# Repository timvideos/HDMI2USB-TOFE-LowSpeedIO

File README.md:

The <a href="http://hdmi2usb.tv/numato-opsis">Numato Opsis</a>, the first open hardware for the
<a href="http://hdmi2usb.tv">HDMI2USB firmware</a>,
<a href="https://numato.com/product/numato-opsis-fpga-based-open-video-platform">can now be ordered from Numato Labs
</a>

## Low Speed I/O - TOFE Expansion board

While the [Numato Opsis board](https://numato.com/product/numato-opsis-fpga-based-open-video-platform)
has a massive amount of high speed I/O interfaces, it doesn't include many
features for interfacing with more pedestrian speed devices such as buttons or
LEDs. To help solve this problem “Low speed I/O” TOFE expansion board was
created.

## Features

The "Low Speed I/O" board has the following features;

 * 1 x Arduino compatible pin header. (With on board ADC enabling analog pins
   support.)

 * 4 x [Digilent Pmod™ Compatible](http://www.digilentinc.com/Pmods/licensing.cfm)
   headers[1] to allow usage of existing expansion boards,
   including boards from 
   [Numato Lab](http://numato.com/fpga-boards/filter/cat/expansion-modules.html?limit=30),
   [Digilent](http://digilentinc.com/pmods),
   [Maxim](https://www.maximintegrated.com/en/design/design-technology/fpga-design-resources/pmod-compatible-plug-in-peripheral-modules.html) and
   [Analog](https://wiki.analog.com/resources/alliances/xilinx#pmods).

 * 1 x USB-UART, allowing low speed serial operation.

 * 6 x Indicator LEDs

 * 4 x Push Buttons

[1]: Two of the Pmod headers share pins with the Arduino header. This means
that when the Arduino compatible pin header is in use only 2 Pmod headers are
available.

A PDF version of schematic can be found in the [docs](docs) directory.

## Editing

The design in this repository was made using [KiCad](http://www.kicad-pcb.org/)
version **2013-07-07 BZR 4022**
([the version is Ubuntu Trusty](http://packages.ubuntu.com/trusty/kicad)).

## License

TOFE Low Speed I/O Expansion board by Numato Systems Pvt. Ltd

The TOFE Low Speed I/O Expansion board is licensed under a
Creative Commons Attribution-ShareAlike 4.0 International License.

You should have received a copy of the license along with this
work. If not, see <http://creativecommons.org/licenses/by-sa/4.0/>.

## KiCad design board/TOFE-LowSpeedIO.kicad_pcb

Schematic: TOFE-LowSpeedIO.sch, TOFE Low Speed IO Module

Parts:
C1, C2: 22pF
C3, C4, C10: 0.1uF
C8, C9: 100uF
D1, D2, D3, D5, D6, D7: LED
D4: DIODE
P1, P2, P3, P4: CONN_6X2
P5: CONN_2
P6: CONN_6
R1, R2, R3, R5, R6, R7, R8, R9: 10K
R4: 680R
R10: 100R
SW1, SW2, SW3, SW4: SW_PUSH
U1: TOFE-8X
U2: AURD_COMM_SHIELD_ZERO_NEW
U3: PIC18F14K50
U5: 7805_NW
X1: CRYSTAL
X2: USBMICRO

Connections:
/12V: D4.1 (A), U1.A2 (12V), U1.A3 (12V), U1.B1 (12V), U1.B2 (12V), U1.B3 (12V)
/A0: U2.9 (A0), U3.9 (RC7/AN9/SDO/T1OSC0)
/A1: U2.10 (A1), U3.8 (RC6/AN8/T13CKI/T1OSC1)
/A2: U2.11 (A2), U3.7 (RC3/AN7/P1C/C12IN3/PGM)
/A3: U2.12 (A3), U3.16 (RC0/AN4/C12IN+/INT0/VREF+)
/A4: U2.13 (A4), U3.15 (RC1/AN5/C12IN1-/INT1/VREF-)
/A5: U2.14 (A5), U3.14 (RC2/AN6/P1D/C12IN2/CVREF/INT2)
/AREF: R3.2, U1.B37 (DIFF_IO_B5P), U2.30 (AREF)
/ATN: U1.A44 (DIFF_IO_A6N), U2.1 (ATN)
/D0: P4.7, U1.B12 (DIFF_IO_YN), U2.15 (0/RX)
/D1: P4.1, U1.B14 (DIFF_IO_B1P), U2.16 (1/TX)
/D2: P4.8, U1.B15 (DIFF_IO_B1N), U2.17 (2)
/D3: P4.2, U1.B19 (DIFF_IO_B2P), U2.18 (3/PWM)
/D4: P4.9, U1.B20 (DIFF_IO_B2N), U2.19 (4)
/D5: P4.3, U1.A19 (DIFF_IO_YP), U2.20 (5/PWM)
/D6: P4.10, U1.B24 (DIFF_IO_B3N), U2.21 (6/PWM)
/D7: P4.4, U1.B23 (DIFF_IO_B3P), U2.22 (7)
/D8: P3.7, U1.B28 (DIFF_CLK_B0N), U2.23 (8)
/D9: P3.1, U1.B27 (DIFF_CLK_B0P), U2.24 (9/PWM)
/D10: P3.8, U1.B30 (DIFF_IO_ZN), U2.25 (10/PWM/SS)
/D11: P3.2, U1.A32 (DIFF_IO_ZP), U2.26 (11/PWM/SPI_MOSI), U2.P4 (SPI_MOSI)
/D12: P3.9, U1.B33 (DIFF_IO_B4P), U2.27 (12/SPI_MIS0), U2.P1 (SPI_MISO)
/D13: P3.3, U1.B34 (DIFF_IO_B4N), U2.28 (13/PWM/SPI_SCK), U2.P3 (SPI_SCK)
/D14: P3.10, U1.B38 (DIFF_IO_B5N), U2.31 (SDA)
/D15: P3.4, U1.B41 (DIFF_IO_B6P), U2.32 (SCL)
/GND: C1.1, C2.1, C3.1, C4.1, C8.2, C9.2, C10.2, D1.2, D2.2, D3.2, D5.2, D6.2, D7.2, P1.5, P1.11, P2.5, P2.11, P3.5, P3.11, P4.5, P4.11, P5.2 (PM), P6.3, R10.2, SW1.2, SW2.2, SW3.2, SW4.2, U1.A4 (GND), U1.A12 (GND), U1.A15 (GND), U1.A18 (GND), U1.A20 (GND), U1.A23 (GND), U1.A24 (GND), U1.A27 (GND), U1.A28 (GND), U1.A31 (GND), U1.A34 (GND), U1.A37 (GND), U1.A38 (GND), U1.A41 (GND), U1.A42 (GND), U1.A45 (GND), U1.A46 (GND), U1.A49 (GND), U1.B4 (GND), U1.B7 (GND), U1.B13 (GND), U1.B16 (GND), U1.B18 (GND), U1.B21 (GND), U1.B22 (GND), U1.B25 (GND), U1.B26 (GND), U1.B29 (GND), U1.B32 (GND), U1.B35 (GND), U1.B36 (GND), U1.B39 (GND), U1.B40 (GND), U1.B43 (GND), U1.B44 (GND), U1.B47 (GND), U1.B49 (GND), U2.6 (GND), U2.7 (GND), U2.29 (GND), U2.P6 (GND), U3.20 (VSS), U5.2 (GND), X2.5 (GND); also elsewhere on the board
/GPIO0_N: P1.7, U1.A6 (DIFF_IO_A0N)
/GPIO0_P: P1.1, U1.A5 (DIFF_IO_A0P)
/GPIO1_N: P1.8, U1.A8 (DIFF_IO_B0N)
/GPIO1_P: P1.2, U1.A7 (DIFF_IO_B0P)
/GPIO2_N: P1.9, U1.A14 (DIFF_CLK_XN)
/GPIO2_P: P1.3, U1.A13 (DIFF_CLK_XP)
/GPIO3_N: P1.10, U1.A17 (DIFF_IO_A1N)
/GPIO3_P: P1.4, U1.A16 (DIFF_IO_A1P)
/GPIO4_N: P2.7, U1.A22 (DIFF_IO_A2N)
/GPIO4_P: P2.1, U1.A21 (DIFF_IO_A2P)
/GPIO5_N: P2.8, U1.A26 (DIFF_IO_A3N)
/GPIO5_P: P2.2, U1.A25 (DIFF_IO_A3P)
/GPIO6_N: P2.9, U1.A30 (DIFF_CLK_A0N)
/GPIO6_P: P2.3, U1.A29 (DIFF_CLK_A0P)
/GPIO7_N: P2.10, U1.A36 (DIFF_IO_A4N)
/GPIO7_P: P2.4, U1.A35 (DIFF_IO_A4P)
/LED1: R5.7, U1.A39 (DIFF_IO_A5P)
/LED2: R5.5, U1.A40 (DIFF_IO_A5N)
/LED3: R5.3, U1.B42 (DIFF_IO_B6N)
/LED4: R5.1, U1.A43 (DIFF_IO_A6P)
/PGC: P6.5, U3.18 (D-/PGC), X2.2 (D-)
/PGD: P6.4, U3.19 (D+/PGD), X2.3 (D+)
/RESET: U1.A11 (~RST), U2.3 (RESET), U2.P5 (RESET)
/RX: U1.B11 (DIFF_IO_XN), U3.12 (RB5/AN11/RX/DT)
/SCL: R8.1, U1.B5 (IDCLK), U3.11 (RB6/SCK/SCL)
/SDA: R9.1, U1.B6 (IDDAT), U3.13 (RB4/AN10/SDI/SDA)
/SW1: R4.7, U1.B45 (DIFF_CLK_B1P)
/SW2: R4.5, U1.B46 (DIFF_CLK_B1N)
/SW3: R4.3, U1.A47 (DIFF_CLK_A1P)
/SW4: R4.1, U1.A48 (DIFF_CLK_A1N)
/TX: U1.B9 (DIFF_IO_XP), U3.10 (RB7/TX/CK)
/VCC3V3: C4.2, P1.6, P1.12, P2.6, P2.12, P3.6, P3.12, P4.6, P4.12, P6.2, R1.1, R3.1, R6.2, R8.2, R9.2, U1.A9 (3V3), U1.A10 (3V3), U1.B8 (3V3), U1.B10 (3V3), U2.4 (3V3), U3.1 (VDD)
/VCC5V: C9.1, C10.1, U2.5 (5V), U2.P2 (5V), U5.3 (VO)
/VCC12V: C8.1, D4.2 (K), U2.8 (VIN), U5.1 (VI)
/VPP: P5.1, P6.1, R1.2, U3.4 (RA3/MCLR/VPP)
unnamed: C1.2, U3.3 (RA4/AN3/OSC2/CLKO), X1.2
unnamed: C2.2, U3.2 (RA5/OSC1/CLKI), X1.1
unnamed: C3.2, U3.17 (VUSB)
unnamed: D1.1, R5.8
unnamed: D2.1, R5.6
unnamed: D3.1, R5.4
unnamed: D5.1, R2.2
unnamed: D6.1, R7.2
unnamed: D7.1, R5.2
unnamed: R2.1, U3.5 (RC5/CCP1/P1A/T0CKI)
unnamed: R4.2, SW4.1
unnamed: R4.4, SW3.1
unnamed: R4.6, SW2.1
unnamed: R4.8, SW1.1
unnamed: R6.1, U2.2 (IOREF)
unnamed: R7.1, U3.6 (RC4/P1B/C12OUT/SRQ)
unnamed: R10.1, X2.1 (VUSB)

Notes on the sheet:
EXPANSION CONNECTORS
PUSH BUTTON SWITCH
LED
ARDUINO ZERO SHIELD
TOFE
12Mhz
ICSP
FWUP
POWER SUPPLY
PIC18F14K50

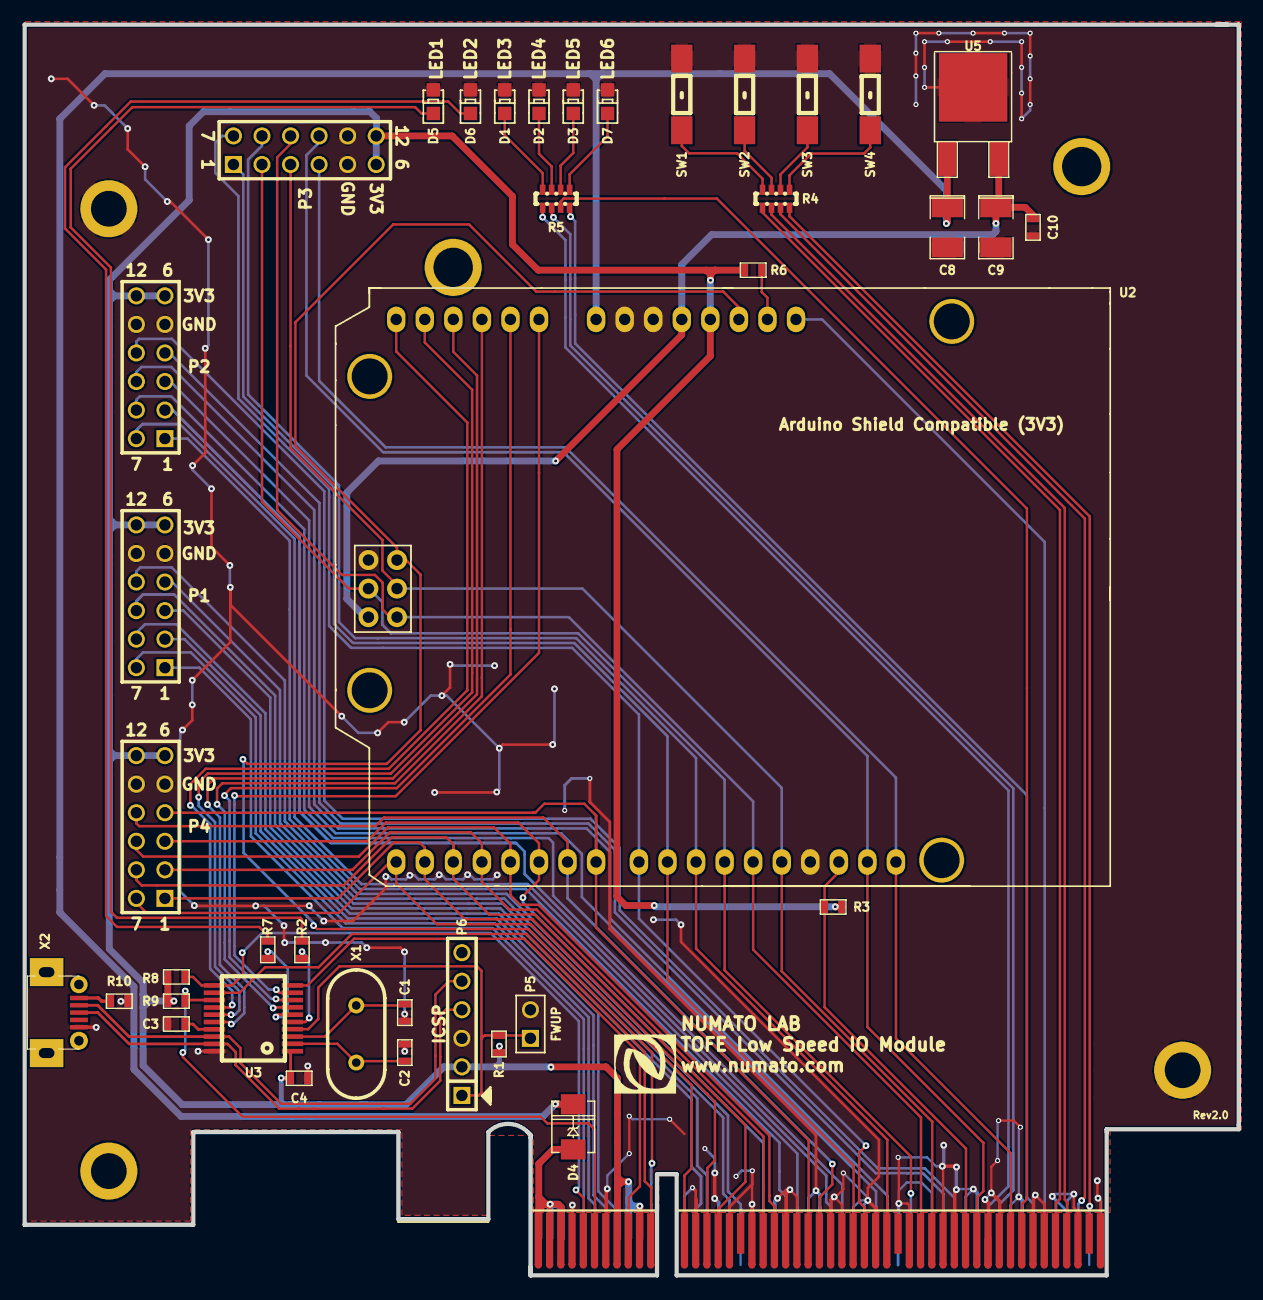
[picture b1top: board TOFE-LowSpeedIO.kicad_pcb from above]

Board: 2 copper layers, 108.0 x 111.2 mm, 42 parts (0 on the bottom side), 78 nets.

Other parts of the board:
1PIN: P***; MH-3.2MM
1PIN#2: P***; 1pin

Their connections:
/GND: 1PIN#2.0; also elsewhere on the board

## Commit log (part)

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2011-12-18 Added eeReadByte() and eeWriteByte() for utilizing the EEPROM. BXR
    Usage:
    eeSetup()
    BP_EE_WP = 0;
    Perform read and writes now.
2011-12-19 Added define functions to enable or disable write protection: // couple defines to enable and disable WP #define eeEnableWrite() BP_EE_WP=0 #define eeDisableWrite() BP_EE_WP=1 #define eeGetWP() BP_EE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
2011-12-19 Enabled the 'h' command for command history. Per Ian I used a define to re-disable it in base.h BP_ENABLE_HISTORY. Seems to be working good so im not sure why it was disabled. but incase it was for a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
2011-12-19 Testing all the small changes for v4 on the v3. I found some small errors in the translation files. Now fixed (project missed the en_US.h include. now fixed works great on v3! BXR
2011-12-19 Updated RC5 decoder as recommended: http://dangerousprototypes.com/forum/viewtopic.php?f=29&t=3342&view=unread#p32861
2011-12-20 v3 reset emulation for testing AVRdude on v4
2011-12-21 AVRDude 40x speedup improvement. WARNING: uses polling of UART bits, will not work on v4 yet! Needs AVRDude patch to work: http://dangerousprototypes.com/forum/viewtopic.php?f=41&t=2629
2011-12-21 bpv4 binary mode reset small fix to include command prompt
2011-12-21 Fixed v4 PPS for LCD, SPI, and UART. AUX pin still needed.
2011-12-22 IR Toy usb stack updates from JTR, fixes 48 byte bug http://dangerousprototypes.com/forum/viewtopic.php?f=29&t=3142&start=15#p33124
2011-12-22 Bus Pirate v3.5e and v4c: centered USB and Connector for both boards LEDs and connectors positions are same on both boards
2011-12-23 Added the 'e' command text to BPMSG instead of bpWline's. BXR
2011-12-25 Changed the Detect Baud rate option to show details so users can see what baud rate was detected and deleted un-needed bpWline messages so no translations needed. BXR
2011-12-26 Deleted a development string I left in base.h. Also renamed the Baud Detection enable define to somthing more understandable. BXR
2011-12-27 part pirate or part ninja silicone tester.
2011-12-28 I checked UART to ensure PPS defines work and UART worked fine. I did not test other peripherals. I also added AUX1 and AUX2 to the PPS controls for hardwarev4a.h
2011-12-28 Cleanup a little bit. Added the on-board EEPROM defines (address,min,max,...). Added the only other broken out PINs PPS (why not) ADC. added 'BP_BUTTON_ISDOWN' define (so you can 'if(BP_BUTTON_ISDOWN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
2011-12-30 Added a 'getlong' function; exactly the same as 'getnumber' but allows a larger MAX value. Enabled on BUSPIRATEV4 ONLY
2011-12-30 Fixed an issue with the new BRG calculation macro and added the text to BPMSG translation files. BXR
2011-12-30 Deleted the BRG calculation macro now that you can input a custom BAUD instead of BRG value now anyways. Deleted translations as they are no longer used. BXR
2012-01-02 Bus Pirate PIC programmer v1c for BPv3
2012-01-04 Connected A10, A11, A12, MEMW and MEMR to CPLD. Texts and labels needs to be fixed
2012-01-04 more updates: moved holes' center 4mm from the corner, holes are not plated, moved push buttons of v4c moved ICSP connectors of v3.5e and v5c moved USB connectors of v3.5e and v5c
2012-01-04 hex2prog added for Bus Pirate bootloader upgrader app
2012-01-04 Bus Pirate documents folder from old SVN
2012-01-04 Edited build-unix.sh and added Linux version for pirate-loader and test script
2012-01-05 BusPirate 4c Sketchup model and one rendering of the same
2012-01-06 Rendering and Sketchup model of the Bus Pirate 3.5e SSOP
2012-01-07 -made adjustments to the labels on the board
2012-01-08 Baud detection updates per Ians v6.1 list. Including: Much smarter 'get nearest common baud' function. MUCH SMARTER Macro still exists for both v3 and v4 hardware Less text used for macro and setup s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
2012-01-09 Bus Pirate SUMP mode fix (made mode variable static again)
2012-01-09 bus pirate hardware version detect
2012-01-09 Bus Pirate bitbang mode IO fix: http://dangerousprototypes.com/forum/viewtopic.php?f=28&t=3403&p=34198#p34196
    Thanks tes!
2012-01-09 defaul unit set to mil, change default trace width to 12mil, drill size to 20. Rename remove_label_layers.scr to hide_label_layers.scr
2012-01-09 Awesome optimization of the get estimated baud function with Arhis help. Same finish but less code to get there. BXR
2012-01-10 Decided there may be more macros or somthing that need to check and offer to match settings. So I moved it into a function UARTmatchSetup(). The function is enabled/disabled by the same define and BP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
2012-01-10 Removal of match baud. BXR
2012-01-12 Just fixed a small warning about unused variable message upon building by putting it behind a hardware version define (BUSPIRATEV2)? in Main.c BXR
2012-01-13 Added SOD-123 package for DIODE device
2012-01-15 Initial programming adapter for BPv4 schematic added, SMPS code does not block other BP functions
2012-01-16 Added LM321 op amp in SOT-23-5 package
2012-01-16 Soldering iron Driver based on arhis Gen3 design
2012-01-17 -updated standard PCB footprints with the latest design
2012-01-18 SOPA PIPA banners
2012-01-18 initial version of the freestanding USB stack, based on the revision 1599 of echo-demo
2012-01-19 removed hole, just plain pad on the 4.1mm round pad package
2012-01-19 Updated standard PCB footprints and added new PCB footprints
2012-01-20 Pic programmer v2 component placement and routing changed for making it smaller
2012-01-23 include grid alternate grid unit, turn-on grid.
2012-01-27 Mass clean-up, rename to a more logical naming. Removed duplicates on symbols and package.
2012-01-30 3d model of the web platform 1.1a
2012-02-02 redesign PCB symbol, added keepout on the DP6037 pcb
2012-02-06 Part Ninja, v1, board, schematic and gerbers
2012-02-06 updated DP6037 standard PCB footprint
2012-02-08 Logo for CC-0 and CC-BY-SA added
2012-02-08 BP4 LCD adapter V4 on a standard case, along with gerbers
2012-02-08 fix 4.1mm round pad, turned on the solder mask "stop" on the pad's property
2012-02-09 updated librarydefaults
2012-02-09 fixed DP10062_V1. removed duplicated holes that gives an error in DRC
2012-02-09 Adding a few SketchUp 3D models.
2012-02-13 Added new board for XTIDE CPLD 3V3 v2a with labels for credits on peitja, J1mbo, alanh and for the Vintage Computer Forums
2012-02-13 Bus Pirate 3.5c sketchup 3d model
2012-02-13 Adding CH375 "USB host Interface Chip" symbol and part to the library the cell SOIC28W already exists. see http://dangerousprototypes.com/forum/viewtopic.php?f=19&t=2657&start=255#p34828
2012-02-14 revered to Jer's 1658 PCBs
2012-02-15 updated v3.5 and v4 board to the new DP6037 standard PCB
2012-02-16 updated BP accessories: HV programming adapter for bus pirate V3 and V4 Made the female IO header location fixed with the Bus Pirate IO header 8.5mm from board edge in x axis.
2012-02-16 updated v1.2 board, moved CC-BY-SA license and OSHW logo to bottom. Made gerber files
2012-02-17 Added BusBlaster-v3.5 board in a standard DP8049 PCB.
2012-02-17 updated XC2C64A v1c and XC9572XL v1b with license CC-0, OSHW and DP logos on the bottom.
2012-02-20 Updated USBPOVToy.v1c board, added logo on the bottom pcb.
2012-02-27 Micro constant Current from SQKYbeaver
2012-02-29 Moveing PIC32Dip files into the hardwar folder insted of root
2012-02-29 PIC32DIP, made some BOM shanges (adjusted the Cap values
2012-03-01 project rebuild, and hex file for the PIC32DIP self test
2012-03-05 Logic Shrimp 3D model
2012-03-07 Updated to the valuse of discrete components on the schematic for Part Ninja
2012-03-07 Updates tot he pic18f2550 schematic, and export files
2012-03-10 Updated the pic24 and pic32 coic28 BB schematic Values
2012-03-12 updated board, widen up spaces, add CC-0 and OSHW logos.
2012-03-12 change version to V1a, board is now consistent on version 1771 schematic.
2012-03-12 Change version to V1a Breakout pin 23 and add Soldering jumper going to 3.3V in case USB mode is used.
2012-03-13 Dangerous Prototypes conference materials
2012-03-13 Map of Cheonggyecheon SVG, and PNG
2012-03-14 Reverted v1's gerber and images. Added v1a gerber and images too.
2012-03-14 reverted v1 board and schematic image and gerber. Added v1a board and schematic image and gerber
2012-03-15 Modification to the Sketchup 3d Models. Adding 2 models, modifying the pinhead models.
2012-03-19 pic32dip partlist wik file
2012-03-26 3d model of picquen32 v1a
2012-03-27 Added Linux Makefile to BPXSVFPlayer folder and compiled binary to package folder
2012-03-28 Demo Mode LED blinking demo for the Bus pirate, zipped up project files
2012-03-28 updates to the BP demo blink led
2012-03-29 update DP eagle library, added ATMEGA32U4, MAX6921. updated the SOIC-28W package to have a larger pads, updated small tactile switch footprint to have a larger pads too. fix center of VFD IV 22 displ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
2012-04-05 Fixes that annoying 'unsued var i' error
2012-04-11 Fix Transistor 5, swapped its collector and emitter.
2012-04-11 PiratePicProg: Fix fatal error, when calling BP_Flush with empty buffer.
2012-04-12 PiratePICProg: Commited patches from AndThen (PIC32MX), PIC32 still needs work. Added verbose debugging print (so far buspirate and serial module). Fixed PIC24 readout support, fixed endiannes of rea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
2012-04-24 renamed bus blaster v3 and v2.7 to match conventions
2012-04-24 updates to SMPS files for binmode usability.
2012-04-25 Buspirate: new PIC programming protocol added to binwire.c
2012-04-26 ATX breakout commit
2012-04-26 yongsan map made in inkscape
2012-04-26 renamed atx v1 breakout eagle files
2012-04-26 Add Standard DP PCB eagle library
2012-04-26 Link to the google SU plugin for exporting faces to SVG.
2012-04-27 Added: USB micro-b, LTC4053, removed eagle lite unsopported DP PCB sizes from dp_pcb.lbr
2012-05-01 Bus Pirate on standard PCB format.
2012-05-01 lcd adapter history file
2012-05-01 Added 3D Parts from my collection
2012-05-01 Bus Pirate v3.6 manufacturing resources
2012-05-02 renameing and small value changes to Bus Blaster v3.5, now V3b. also added new gerbers, partlist, and quote package. v3,5 removed
2012-05-02 Bus Blaster v3 JTAGkey buffer with self test
2012-05-02 Added integrated support of XSVF player for BPv4 only Added Windows side XSVF Player for BPv4 only (Built with Dev-C++) Has been based on previous specific BPv3 XSVF player (firmware-XSVFplayer)
2012-05-04 Bus Pirate firmware merged with JTR's 7 stack version. USB stack updated.
2012-05-04 Bus Pirate v4 firmware update. fixed type in USB stack. Fixed include in project file.
2012-05-04 JTR 7 stack echo demo initial add
2012-05-04 Added USB echo demo for logic sniffer (18F24J50). Not working.
2012-05-08 New files for IR Toy with v.2a USB stack
2012-05-08 Final IR Toy JTR stack update commit
2012-05-08 moved old POV Toy firmwares to attic
2012-05-09 Archive of the stack, and the exporte echo demo for the BP.
2015-10-14 Adding information about board shape.
2015-10-14 Starting to get directory structure set up.
2015-10-14 Adding some pictures.
2015-10-14 Updating the PCB with dimensions.
    Fixes #2.
2015-10-15 Adding script to quickly rename the schematic.
2015-10-15 Temp commit.
2015-10-15 Fixing the EEPROM pin connections.
2015-10-15 Adding schematic and deleting old images.
2015-11-04 Changes on 2015-11-03.
2015-11-04 Fixing for TOFE part update.
2015-12-22 Gerber files sent to production.
2015-12-28 Fixing for Microchip HID bootloader.
2015-12-28 Major cleanup of the cdc.c file
    * Naming things consistently.
    * All state variables starts with cdcdata_XXXXX
    * All functions start with cdc_xxxx
    Getting ready to make a "dual CDC" device.
2015-12-28 Customizing the strings and VID/PID values.
2015-12-28 Adding README and LICENSE file.
2015-12-28 Adding flash script.
2015-12-28 Kinda working dual CDC ports.
2015-12-28 Adding uart which connects to the first serial port.
    Currently hard coded at 9600 baud.
2015-12-28 Adding command line interface to PIC UART.
2015-12-31 Adding a cdc command for sending a string.
2015-12-31 Flash script will wait for the microchip device to appear.
2015-12-31 Working on the PIC command line.
2016-01-01 Fixing signed comparison.
2016-01-01 Adding the LED commands.
    Fixes #15.
2016-01-05 Adding git version information.
2016-01-05 Adding real TOFE data.
2016-01-06 Making the LED code work.
2016-01-06 PICKit config.
2016-01-06 Enable USB errors to reboot the stack.
2016-01-06 Device is self powered.
2016-01-06 Enable watchdog.
2016-01-06 Adding README for the driver directory.
2016-01-08 Fixing missing channel 5.
2016-01-11 Improving the comments.
2016-05-26 Adding a link to the schematic.
2016-05-26 Fixing the schematic docs link.
2016-09-24 Trying to fix the Pmod connector labeling.
2016-09-24 Add missing fp-lib-table file.

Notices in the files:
board/TOFE-LowSpeedIO.kicad_pcb:
License : CC BY-SA
board/TOFE-LowSpeedIO.sch:
License: CC-BY-SA 4.0 International
